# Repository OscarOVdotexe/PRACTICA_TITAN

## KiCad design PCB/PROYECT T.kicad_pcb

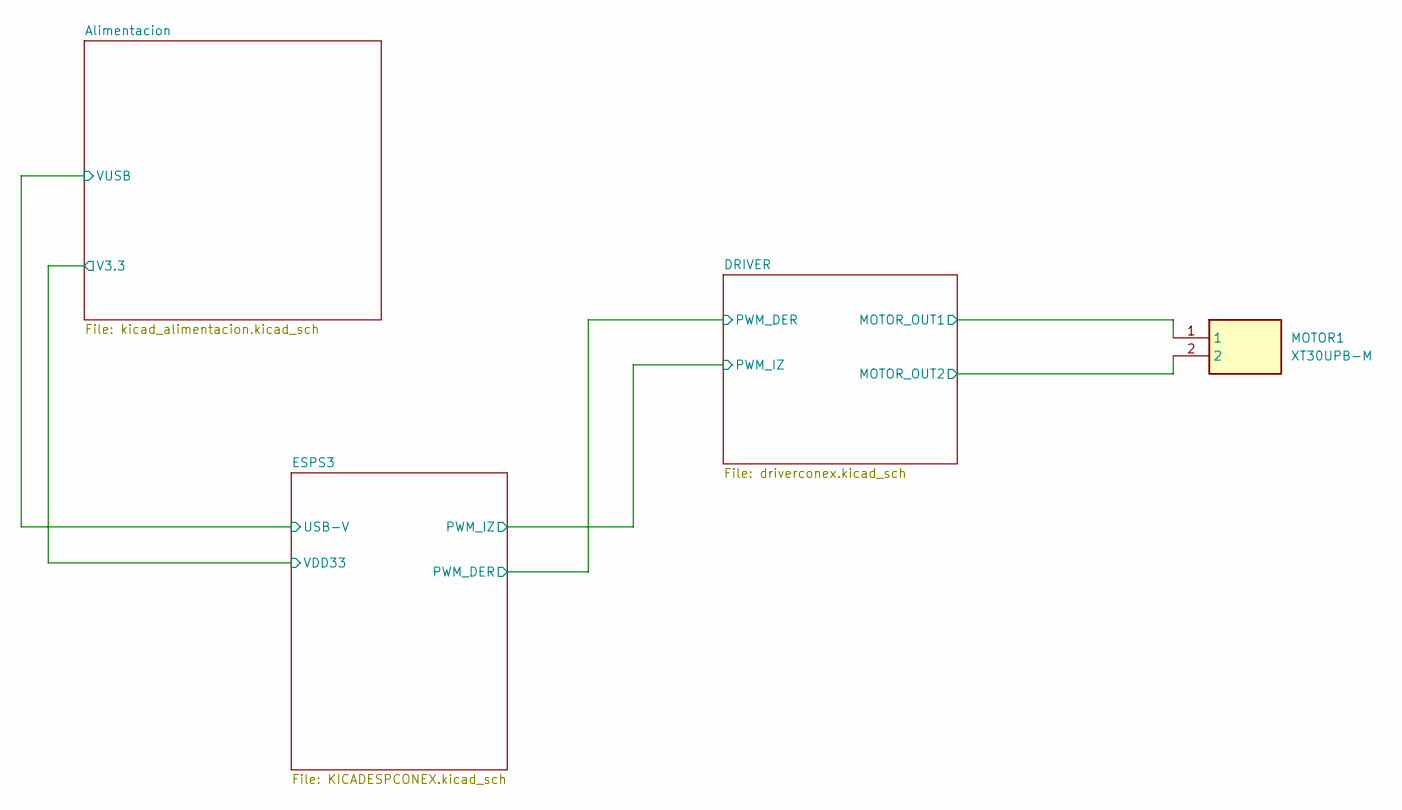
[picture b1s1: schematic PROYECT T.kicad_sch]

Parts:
MOTOR1: XT30UPB-M; SHDR2W160P0X500_1X2_1020X520X1070P; Manufacturer_Part_Number XT30UPB-M

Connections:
/DRIVER/MOTOR_OUT1: MOTOR1.1; also elsewhere on the board
/DRIVER/MOTOR_OUT2: MOTOR1.2; also elsewhere on the board

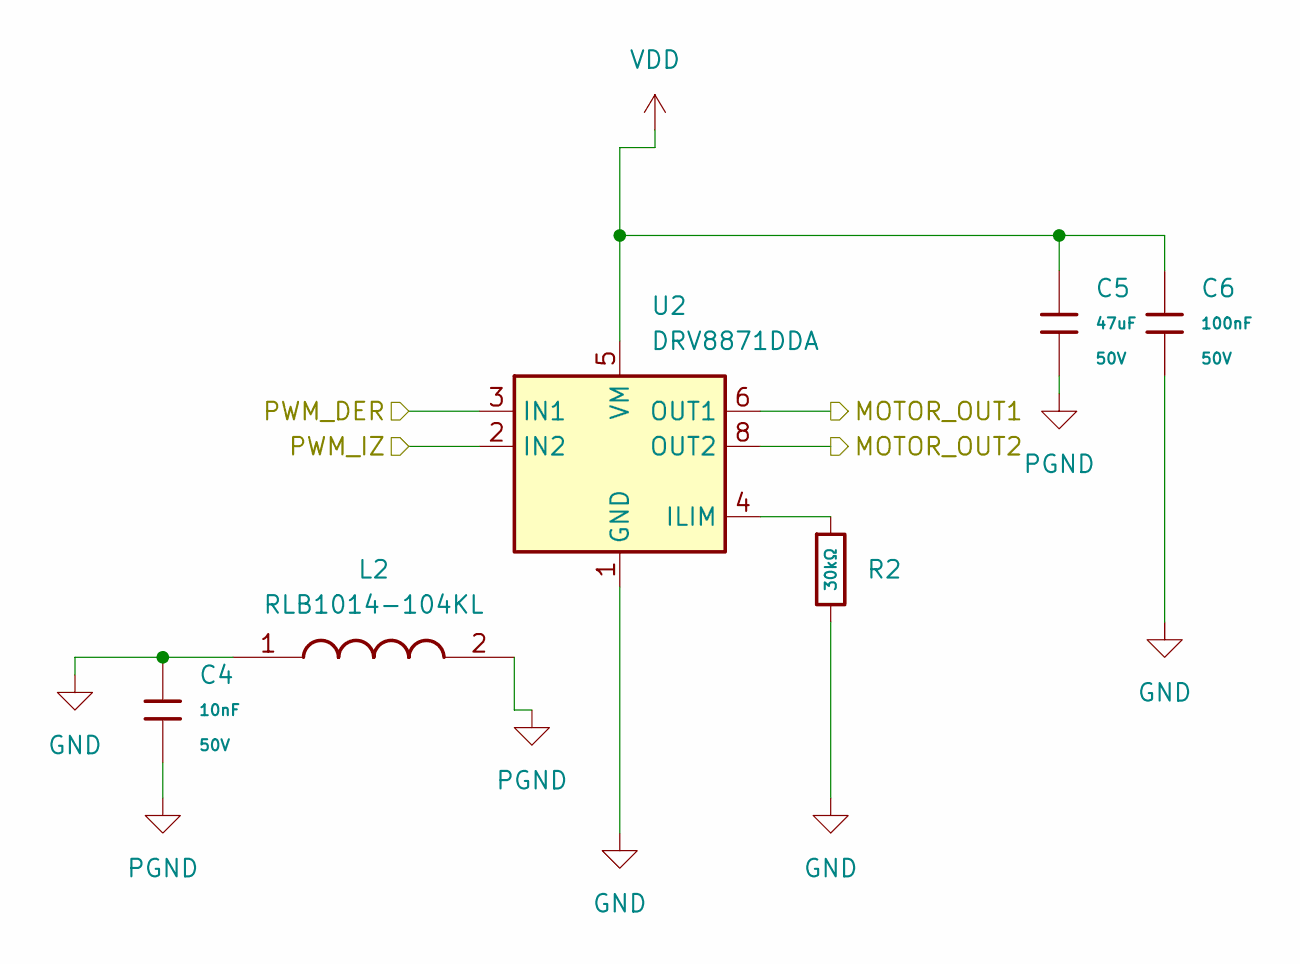
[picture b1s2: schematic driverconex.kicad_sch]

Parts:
C4: 10nF; C_0402; Voltage Rated 50V; Tolerance ±10%; Part CL05B103KB5NNNC; LCSC C15195
C5: 47uF; C_Elec_6.3x7.7; Voltage Rated 50V; Tolerance ±20%; Part CL21A476MQYNNNE; LCSC C16780
C6: 100nF; C_0603; Voltage Rated 50V; Tolerance ±10%; Part CC0603KRX7R9BB104; LCSC C14663
L2: RLB1014-104KL; RLB1014104KL; Manufacturer_Part_Number RLB1014-104KL; Mouser Part Number 652-RLB1014-104KL
R2: 30kΩ; R_0603; Overload Voltage (Max) 75V; Tolerance ±1%; Part 0603WAF3002T5E; LCSC C22984
U2: DRV8871DDA; Texas_HTSOP-8-1EP_3.9x4.9mm_P1.27mm_EP2.95x4.9mm_Mask2.4x3.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

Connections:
/DRIVER/MOTOR_OUT1: U2.6 (OUT1); also elsewhere on the board
/DRIVER/MOTOR_OUT2: U2.8 (OUT2); also elsewhere on the board
/DRIVER/PWM_DER: U2.3 (IN1); also elsewhere on the board
/DRIVER/PWM_IZ: U2.2 (IN2); also elsewhere on the board
GND: C4.1, C6.2, L2.1, R2.2, U2.1 (GND), U2.7 (GND), U2.9 (GND); also elsewhere on the board
unnamed: R2.1, U2.4 (ILIM)
PGND: C4.2, C5.2, L2.2
VDD: C5.1, C6.1, U2.5 (VM); also elsewhere on the board

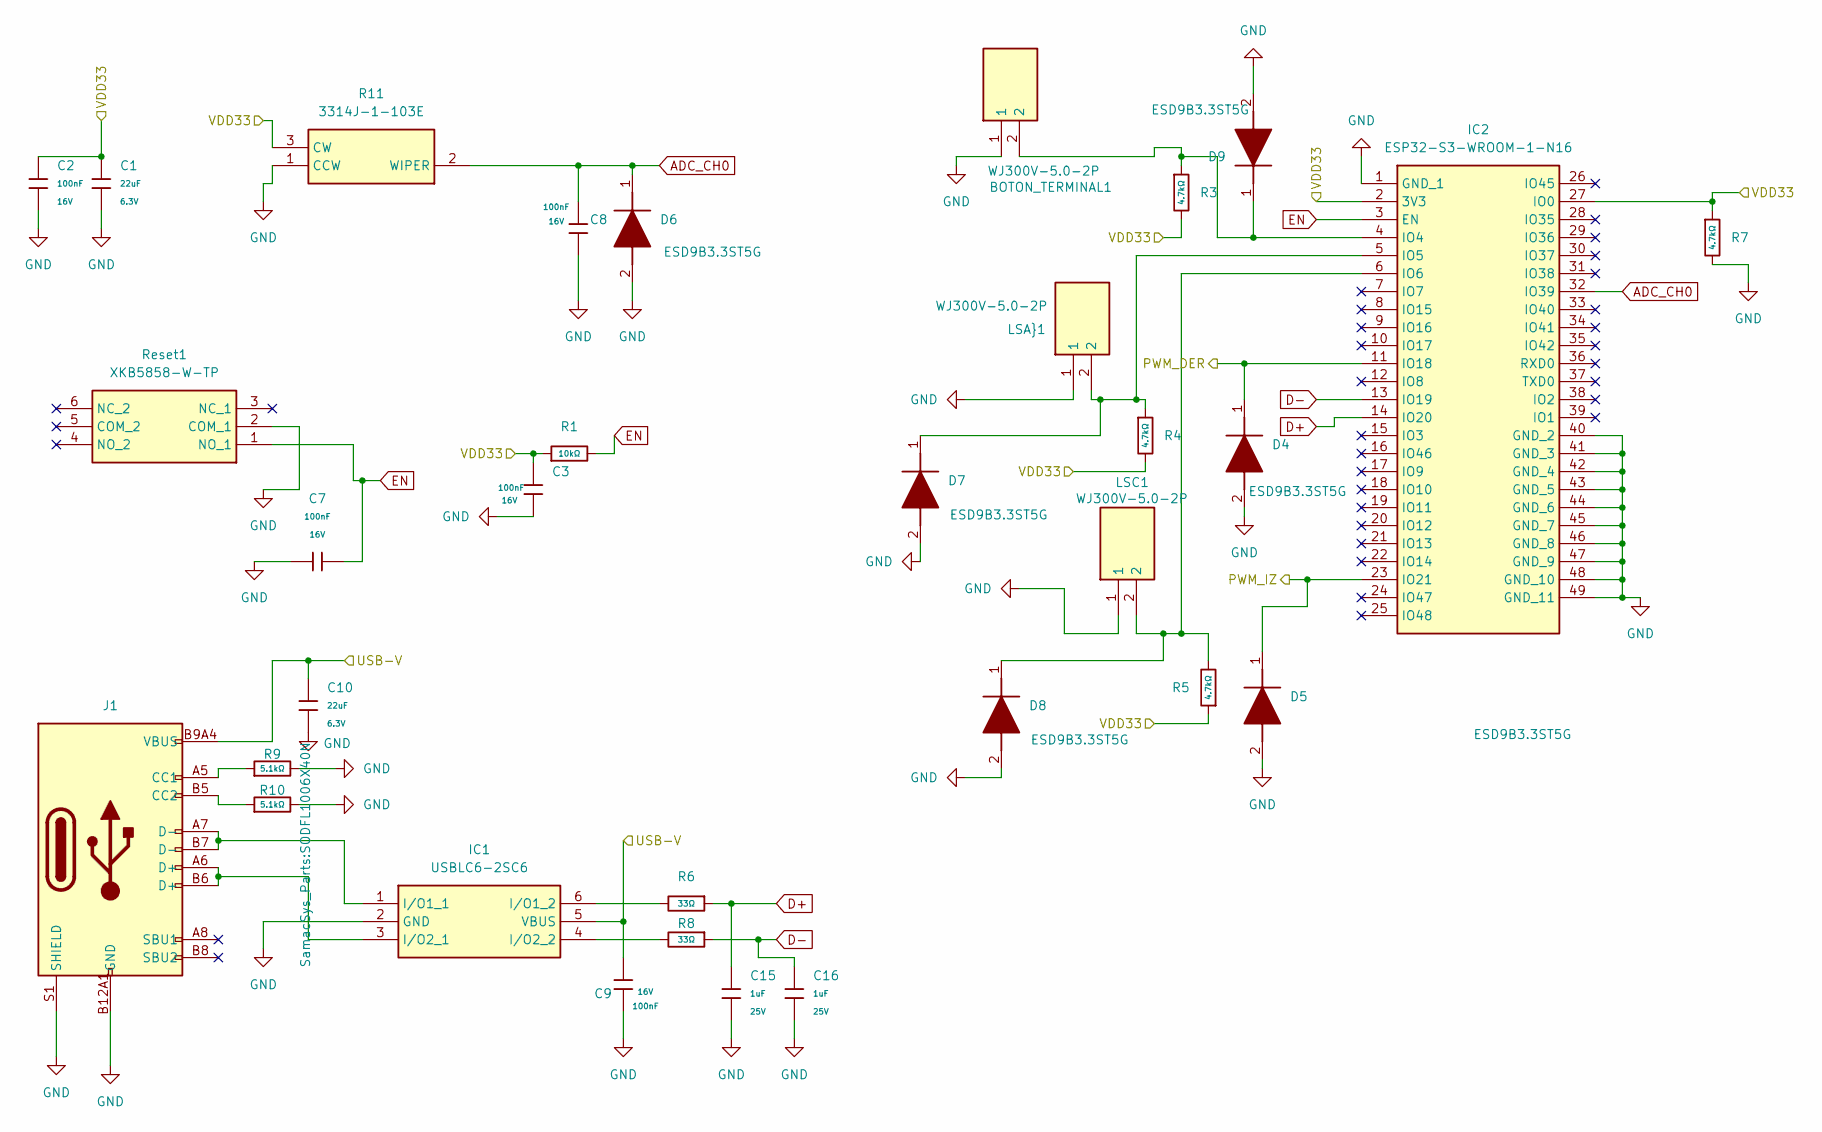
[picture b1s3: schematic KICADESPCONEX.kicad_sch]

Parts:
BOTON_TERMINAL1: WJ300V-5.0-2P; SHDR2W105P0X500_1X2_1000X900X1260P; Manufacturer_Part_Number WJ300V-5.0-2P
C1, C10: 22uF; C_0603; Voltage Rated 6.3V; Tolerance ±20%; Part CL10A226MQ8NRNC; LCSC C59461
C2, C3, C7, C8, C9: 100nF; C_0402; Voltage Rated 16V; Tolerance ±10%; Part CL05B104KO5NNNC; LCSC C1525
C15, C16: 1uF; C_0402; Voltage Rated 25V; Tolerance ±10%; Part CL05A105KA5NQNC; LCSC C52923
D4, D5, D6, D7, D8, D9: ESD9B3.3ST5G; SODFL1006X40N; Manufacturer_Part_Number ESD9B3.3ST5G; Mouser Part Number 863-ESD9B3.3ST5G
IC1: USBLC6-2SC6; SOT95P280X145-6N; Manufacturer_Part_Number USBLC6-2SC6; Mouser Part Number 511-USBLC6-2SC6
IC2: ESP32-S3-WROOM-1-N16; ESP32S3WROOM1N16; Manufacturer_Part_Number ESP32-S3-WROOM-1-N16; Mouser Part Number 356-ESP32S3WROOM1N16
J1: Connector, USB-TYPE-C-16P; TYPE-C-SMD_HX-TYPE-C-16PIN; LCSC C2927039
LSA}1: WJ300V-5.0-2P; SHDR2W105P0X500_1X2_1000X900X1260P; Manufacturer_Part_Number WJ300V-5.0-2P
LSC1: WJ300V-5.0-2P; SHDR2W105P0X500_1X2_1000X900X1260P; Manufacturer_Part_Number WJ300V-5.0-2P
R1: 10kΩ; R_0402; Overload Voltage (Max) 50V; Tolerance ±1%; Part 0402WGF1002TCE; LCSC C25744
R3, R4, R5, R7: 4.7kΩ; R_0402; Overload Voltage (Max) 50V; Tolerance ±1%; Part 0402WGF4701TCE; LCSC C25900
R6, R8: 33Ω; R_0402; Overload Voltage (Max) 50V; Tolerance ±1%; Part 0402WGF330JTCE; LCSC C25105
R9, R10: 5.1kΩ; R_0805; Overload Voltage (Max) 150V; Tolerance ±1%; Part 0805W8F5101T5E; LCSC C27834
R11: 3314J-1-103E; 3314J-1; Manufacturer_Part_Number 3314J-1-103E; Mouser Part Number 652-3314J-1-103E
Reset1: XKB5858-W-TP; XKB5858WTP; Manufacturer_Part_Number XKB5858-W-TP

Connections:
/Alimentacion/V3.3: C1.1, C2.1, C3.1, IC2.2 (3V3), IC2.27 (IO0), R1.1, R3.2, R4.2, R5.1, R7.1, R11.3 (CW); also elsewhere on the board
/Alimentacion/VUSB: C9.2, C10.1, IC1.5 (VBUS), J1.A9B4 (VBUS), J1.B9A4 (VBUS); also elsewhere on the board
/DRIVER/PWM_DER: D4.1 (K), IC2.11 (IO18); also elsewhere on the board
/DRIVER/PWM_IZ: D5.1 (K), IC2.23 (IO21); also elsewhere on the board
ADC_CH0: C8.1, D6.1 (K), IC2.32 (IO39), R11.2 (WIPER)
D+: C15.1, IC2.14 (IO20), R6.1
D-: C16.1, IC2.13 (IO19), R8.1
EN: C7.2, IC2.3 (EN), R1.2, Reset1.1 (NO_1)
GND: BOTON_TERMINAL1.1, C1.2, C2.2, C3.2, C7.1, C8.2, C9.1, C10.2, C15.2, C16.2, D4.2 (A), D5.2 (A), D6.2 (A), D7.2 (A), D8.2 (A), D9.2 (A), IC1.2 (GND), IC2.1 (GND_1), IC2.40 (GND_2), IC2.41 (GND_3), IC2.42 (GND_4), IC2.43 (GND_5), IC2.44 (GND_6), IC2.45 (GND_7), IC2.46 (GND_8), IC2.47 (GND_9), IC2.48 (GND_10), IC2.49 (GND_11), J1.A12B1 (GND), J1.B12A1 (GND), J1.S1 (SHIELD), LSA}1.1, LSC1.1, R7.2, R9.2, R10.2, R11.1 (CCW), Reset1.2 (COM_1); also elsewhere on the board
unnamed: D7.1 (K), IC2.5 (IO5), LSA}1.2, R4.1
unnamed: D8.1 (K), IC2.6 (IO6), LSC1.2, R5.2
unnamed: BOTON_TERMINAL1.2, D9.1 (K), IC2.4 (IO4), R3.1
unnamed: IC1.1 (I/O1_1), J1.A7 (D-), J1.B7 (D-)
unnamed: IC1.6 (I/O1_2), R6.2
unnamed: IC1.3 (I/O2_1), J1.A6 (D+), J1.B6 (D+)
unnamed: IC1.4 (I/O2_2), R8.2
unnamed: J1.A5 (CC1), R9.1
unnamed: J1.B5 (CC2), R10.1

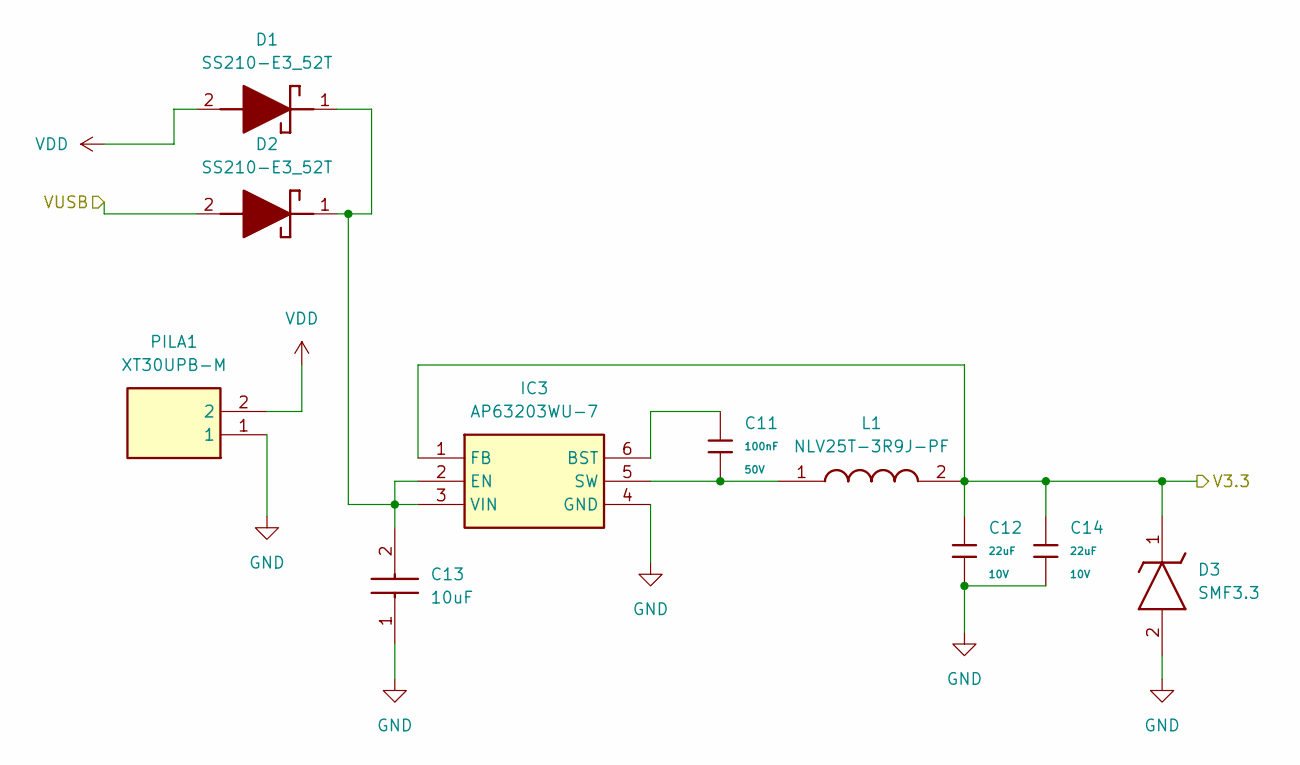
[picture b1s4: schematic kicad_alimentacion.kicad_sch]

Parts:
C11: 100nF; C_0603; Voltage Rated 50V; Tolerance ±10%; Part CC0603KRX7R9BB104; LCSC C14663
C12, C14: 22uF; C_1206; Voltage Rated 10V; Tolerance ±10%; Part CL31A226KPHNNNE; LCSC C5672
C13: 10uF; CAPC3216X180N; Manufacturer_Part_Number CL31A106KBHNNNE; Mouser Part Number 187-CL31A106KBHNNNE
D1, D2: SS210-E3_52T; DIONM5436X244N; Manufacturer_Part_Number SS210-E3/52T; Mouser Part Number 625-SS210-E3
D3: SMF3.3; SOD3718X108N; Manufacturer_Part_Number SMF3.3; Mouser Part Number 576-SMF3.3
IC3: AP63203WU-7; AP63203WU7; Manufacturer_Part_Number AP63203WU-7; Mouser Part Number 621-AP63203WU-7
L1: NLV25T-3R9J-PF; INDM2520X190N; Manufacturer_Part_Number NLV25T-3R9J-PF; Mouser Part Number 810-NLV25T-3R9J
PILA1: XT30UPB-M; SHDR2W160P0X500_1X2_1020X520X1070P; Manufacturer_Part_Number XT30UPB-M

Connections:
/Alimentacion/V3.3: C12.1, C14.1, D3.1 (K), IC3.1 (FB), L1.2; also elsewhere on the board
/Alimentacion/VUSB: D2.2 (A); also elsewhere on the board
GND: C12.2, C13.1, C14.2, D3.2 (A), IC3.4 (GND), PILA1.1; also elsewhere on the board
unnamed: C13.2, D1.1 (K), D2.1 (K), IC3.2 (EN), IC3.3 (VIN)
unnamed: C11.1, IC3.6 (BST)
unnamed: C11.2, IC3.5 (SW), L1.1
VDD: D1.2 (A), PILA1.2; also elsewhere on the board

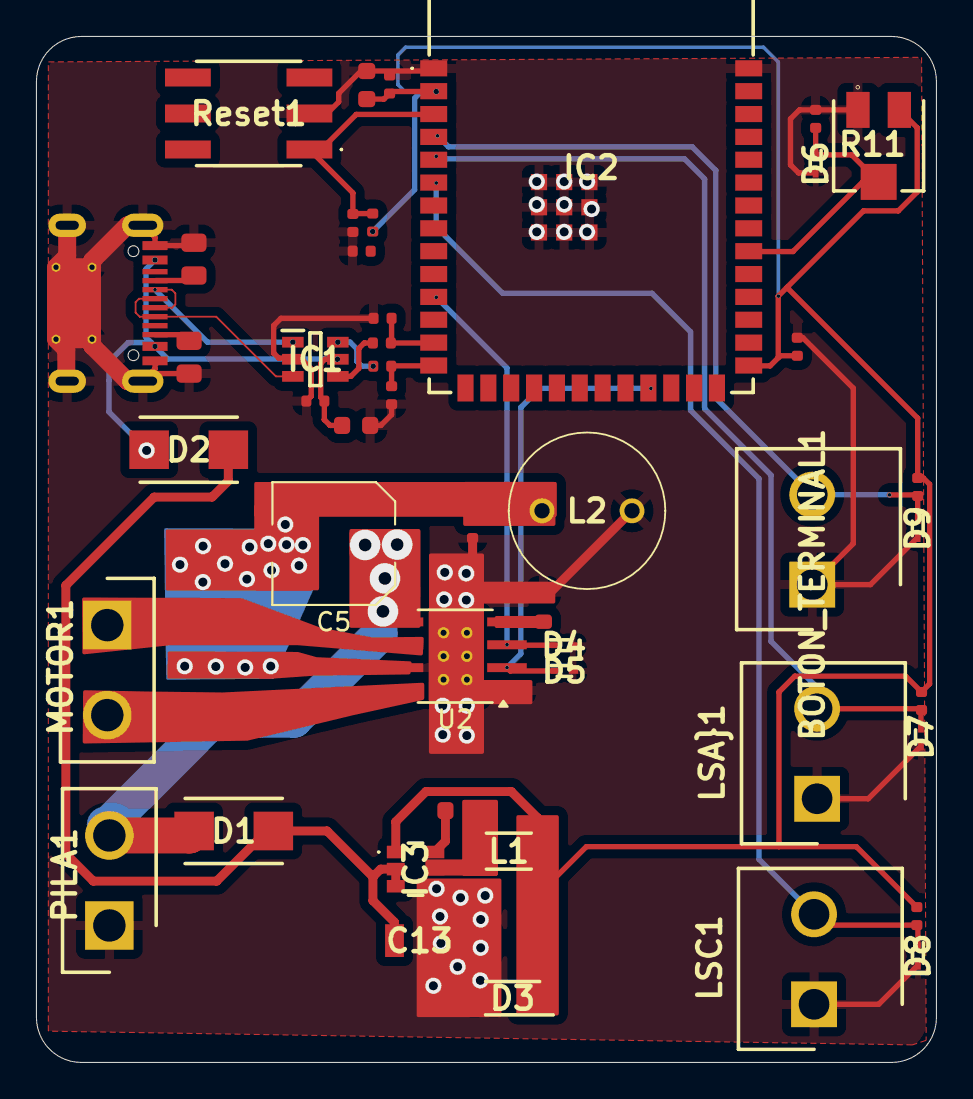
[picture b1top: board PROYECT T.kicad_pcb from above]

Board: 2 copper layers, 50.0 x 57.0 mm, 49 parts (0 on the bottom side), 26 nets.

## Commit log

2025-02-27 Create DESCRIPCION
